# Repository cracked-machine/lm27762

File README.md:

Replaced RP1 with [C2759535](https://www.lcsc.com/product-detail/Chip-Resistor-Surface-Mount_UNI-ROYAL-Uniroyal-Elec-HP02WAF1002TCE_C2759535.html)

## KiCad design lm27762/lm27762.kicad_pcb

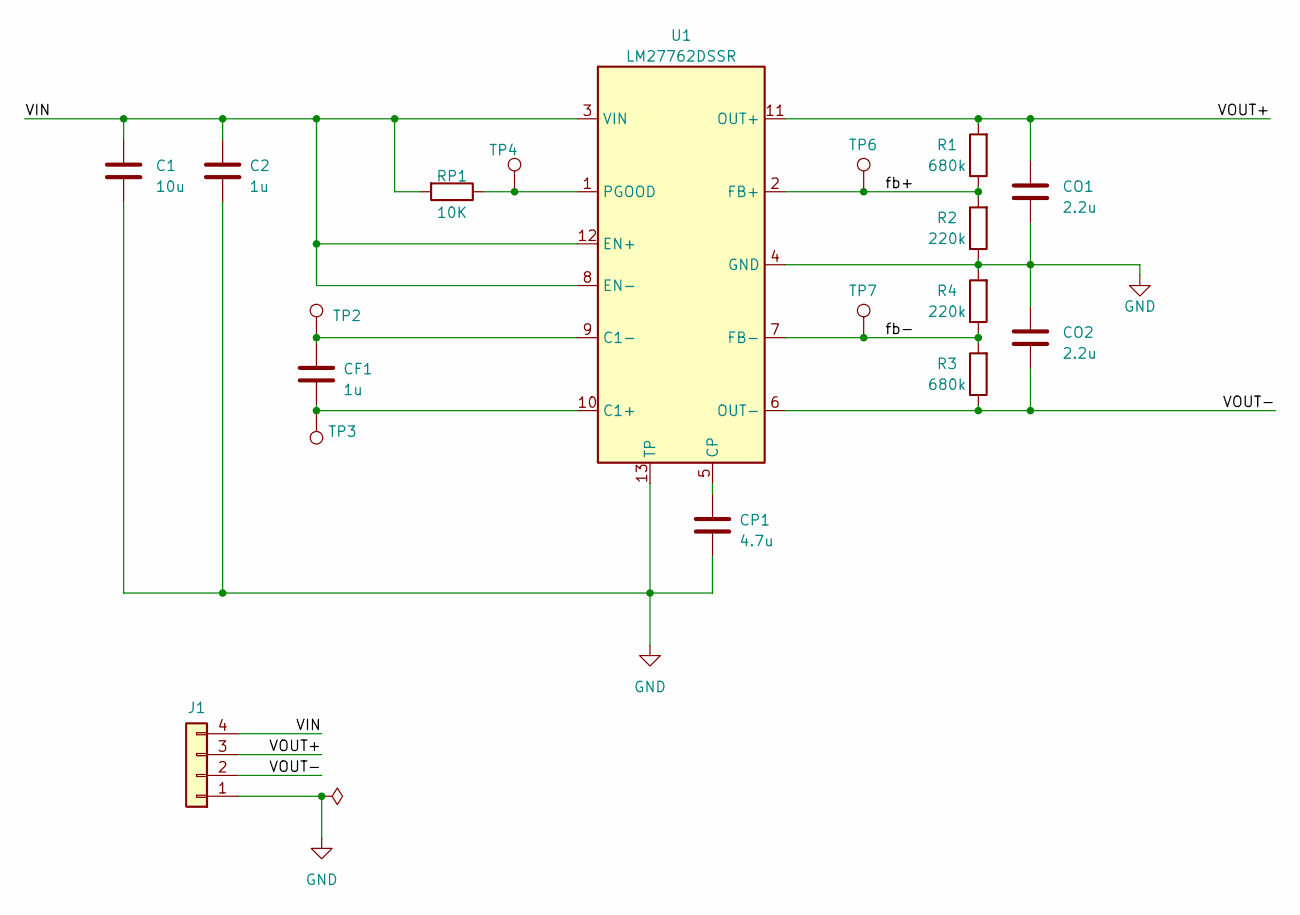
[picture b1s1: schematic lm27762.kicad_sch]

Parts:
C1: 10u; C_0603_1608Metric_Pad1.08x0.95mm_HandSolder; MPN CL10A106MP8NNNC; LCSC C85713
C2: 1u; C_0402_1005Metric_Pad0.74x0.62mm_HandSolder; MPN CL05A105KA5NQNC; LCSC C52923
CF1: 1u; C_0402_1005Metric_Pad0.74x0.62mm_HandSolder; MPN CL05A105KP5NNNC; LCSC C14445
CO1, CO2: 2.2u; C_0603_1608Metric_Pad1.08x0.95mm_HandSolder; MPN CL10A225KP8NNNC; LCSC C1607
CP1: 4.7u; C_0603_1608Metric_Pad1.08x0.95mm_HandSolder; MPN CL10A475KP8NNNC; LCSC C1705
J1: Conn_01x04; PinHeader_1x04_P2.54mm_Vertical
R1, R3: 680k; R_0603_1608Metric_Pad0.98x0.95mm_HandSolder; MPN RC0603FR-07680KL; LCSC C137690
R2, R4: 220k; R_0603_1608Metric_Pad0.98x0.95mm_HandSolder; MPN RC0603FR-07220KL; LCSC C123420
RP1: 10K; R_0402_1005Metric_Pad0.72x0.64mm_HandSolder; MPN ERJ2RKF1002X; LCSC C191123
TP2, TP3, TP4, TP6, TP7: TestPoint; 0_5mm
U1: LM27762DSSR; WSON-12-1EP_3x2mm_P0.5mm_EP1x2.65_ThermalVias; MPN LM27762DSSR; LCSC C473398

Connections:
/VIN: C1.1, C2.2, J1.4, RP1.2, U1.3 (VIN), U1.8 (EN-), U1.12 (EN+)
/VOUT+: CO1.2, J1.3, R1.2, U1.11 (OUT+)
/VOUT-: CO2.1, J1.2, R3.1, U1.6 (OUT-)
/fb+: R1.1, R2.2, TP6.1, U1.2 (FB+)
/fb-: R3.2, R4.1, TP7.1, U1.7 (FB-)
GND: C1.2, C2.1, CO1.1, CO2.2, CP1.1, J1.1, R2.1, R4.2, U1.4 (GND), U1.13 (TP)
unnamed: CF1.1, TP3.1, U1.10 (C1+)
unnamed: CF1.2, TP2.1, U1.9 (C1-)
unnamed: CP1.2, U1.5 (CP)
unnamed: RP1.1, TP4.1, U1.1 (PGOOD)

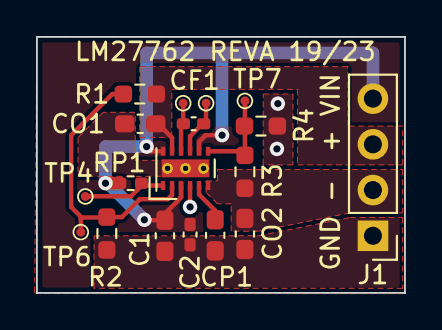
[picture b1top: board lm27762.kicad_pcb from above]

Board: 2 copper layers, 20.4 x 14.2 mm, 18 parts (0 on the bottom side), 10 nets.

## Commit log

2023-05-07 init
2023-05-07 added schema
2023-05-08 removed backups
2023-05-08 added datasheets
2023-05-08 updated tiny testpoints
2023-05-08 moved symbol file to kicad library submodule
2023-05-08 renamed schema file
2023-05-08 updated design files to RevA
2023-05-08 generated production files
2023-05-08 add component replcement note
2023-05-08 ignore kicad backup files
2023-05-08 updated submodule
